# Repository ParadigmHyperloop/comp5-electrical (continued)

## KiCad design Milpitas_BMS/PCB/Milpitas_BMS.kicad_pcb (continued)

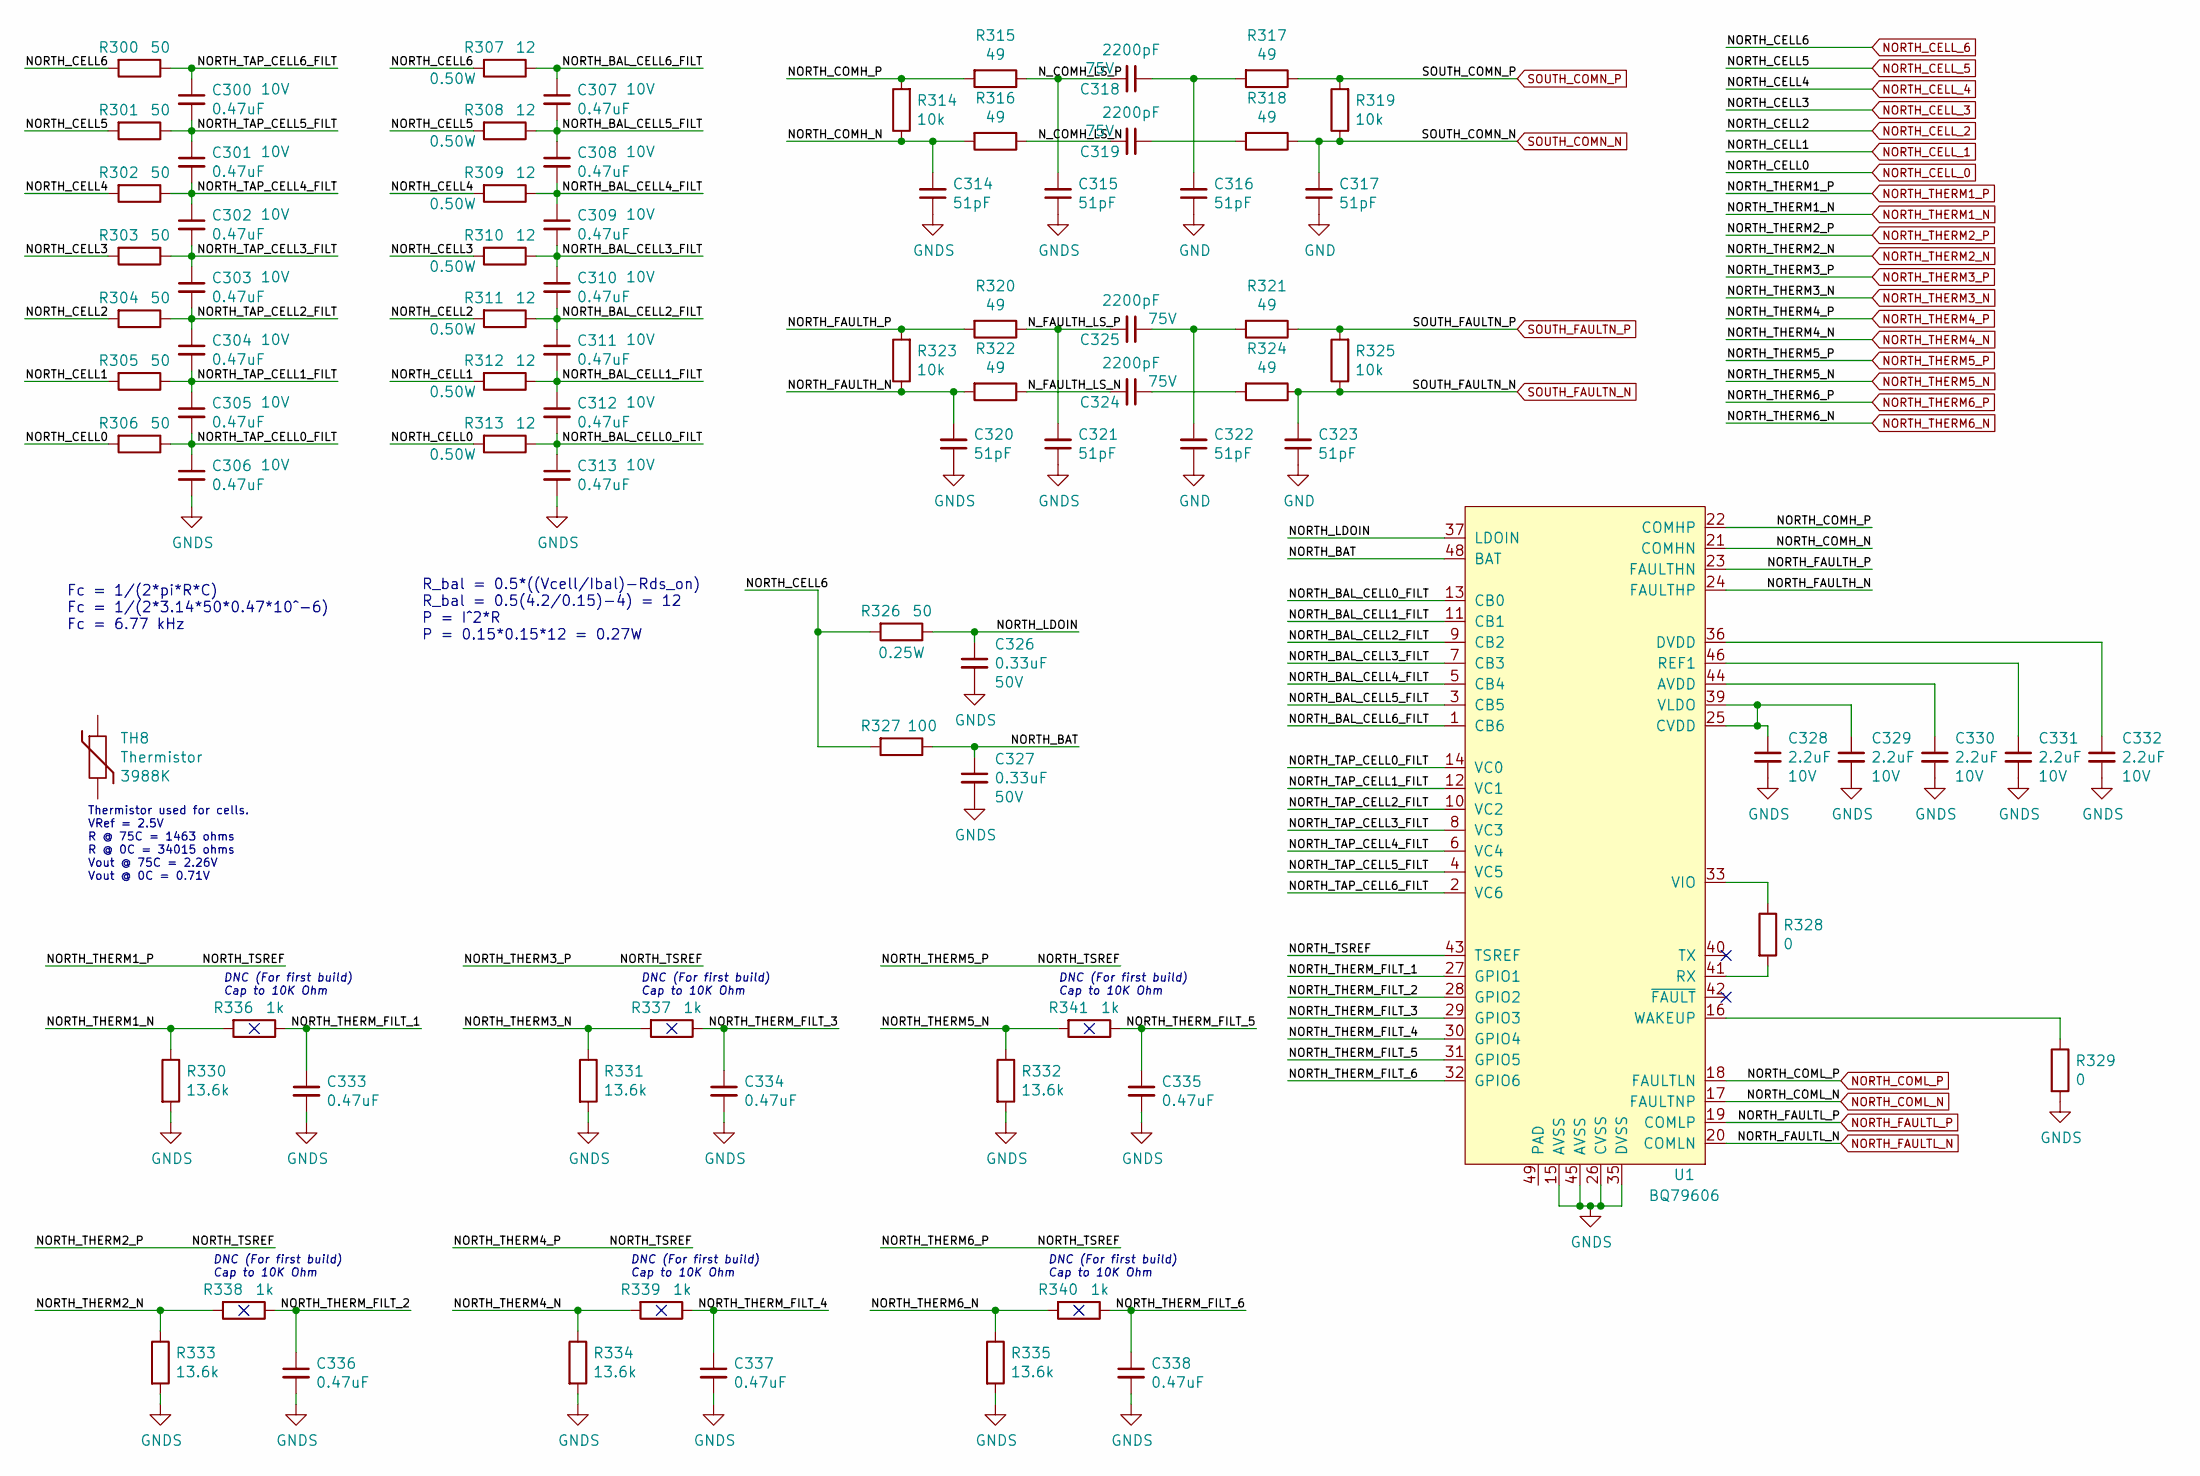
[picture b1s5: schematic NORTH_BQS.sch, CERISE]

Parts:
C300, C301, C302, C303, C304, C305, C306, C307, C308, C309, C310, C311, C312, C313: 0.47uF; C_0603_1608Metric; Voltage 10V
C314, C315, C316, C317, C320, C321, C322, C323: 51pF; C_0603_1608Metric
C318, C319, C324, C325: 2200pF; C_0603_1608Metric; Voltage 75V
C326, C327: 0.33uF; C_0603_1608Metric; Voltage 50V
C328, C329, C330, C331, C332: 2.2uF; C_0603_1608Metric; Voltage 10V
C333, C334, C335, C336, C337, C338: 0.47uF; C_0603_1608Metric
R300, R301, R302, R303, R304, R305, R306, R326: 50; R_0603_1608Metric
R307, R308, R309, R310, R311, R312, R313: 12; R_0603_1608Metric
R314, R319, R323, R325: 10k; R_0603_1608Metric
R315, R316, R317, R318, R320, R321, R322, R324: 49; R_0603_1608Metric
R327: 100; R_0603_1608Metric
R328, R329: 0; R_0603_1608Metric
R330, R331, R332, R333, R334, R335: 13.6k; R_0603_1608Metric
R336, R337, R338, R339, R340, R341: 1k; R_0603_1608Metric
TH8: Thermistor
U1: BQ79606; LQFP-48-1EP_7x7mm_P0.5mm_EP3.6x3.6mm_ThermalVias; Digikey 296-BQ79606APHPTQ1CT-ND

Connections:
/NORTH_BQ/NORTH_BAL_CELL0_FILT: C312.2, C313.1, R313.1, U1.13 (CB0)
/NORTH_BQ/NORTH_BAL_CELL1_FILT: C311.2, C312.1, R312.1, U1.11 (CB1)
/NORTH_BQ/NORTH_BAL_CELL2_FILT: C310.2, C311.1, R311.1, U1.9 (CB2)
/NORTH_BQ/NORTH_BAL_CELL3_FILT: C309.2, C310.1, R310.1, U1.7 (CB3)
/NORTH_BQ/NORTH_BAL_CELL4_FILT: C308.2, C309.1, R309.1, U1.5 (CB4)
/NORTH_BQ/NORTH_BAL_CELL5_FILT: C307.2, C308.1, R308.1, U1.3 (CB5)
/NORTH_BQ/NORTH_BAL_CELL6_FILT: C307.1, R307.1, U1.1 (CB6)
/NORTH_BQ/NORTH_BAT: C327.1, R327.1, U1.48 (BAT)
/NORTH_BQ/NORTH_COMH_N: C314.2, R314.1, R316.2, U1.21 (COMHN)
/NORTH_BQ/NORTH_COMH_P: R314.2, R315.2, U1.22 (COMHP)
/NORTH_BQ/NORTH_FAULTH_N: C320.2, R322.2, R323.1, U1.24 (FAULTHP)
/NORTH_BQ/NORTH_FAULTH_P: R320.2, R323.2, U1.23 (FAULTHN)
/NORTH_BQ/NORTH_LDOIN: C326.1, R326.1, U1.37 (LDOIN)
/NORTH_BQ/NORTH_TAP_CELL0_FILT: C305.2, C306.1, R306.1, U1.14 (VC0)
/NORTH_BQ/NORTH_TAP_CELL1_FILT: C304.2, C305.1, R305.1, U1.12 (VC1)
/NORTH_BQ/NORTH_TAP_CELL2_FILT: C303.2, C304.1, R304.1, U1.10 (VC2)
/NORTH_BQ/NORTH_TAP_CELL3_FILT: C302.2, C303.1, R303.1, U1.8 (VC3)
/NORTH_BQ/NORTH_TAP_CELL4_FILT: C301.2, C302.1, R302.1, U1.6 (VC4)
/NORTH_BQ/NORTH_TAP_CELL5_FILT: C300.2, C301.1, R301.1, U1.4 (VC5)
/NORTH_BQ/NORTH_TAP_CELL6_FILT: C300.1, R300.1, U1.2 (VC6)
/NORTH_BQ/NORTH_THERM_FILT_1: C333.1, R336.1, U1.27 (GPIO1)
/NORTH_BQ/NORTH_THERM_FILT_2: C336.1, R338.1, U1.28 (GPIO2)
/NORTH_BQ/NORTH_THERM_FILT_3: C334.1, R337.1, U1.29 (GPIO3)
/NORTH_BQ/NORTH_THERM_FILT_4: C337.1, R339.1, U1.30 (GPIO4)
/NORTH_BQ/NORTH_THERM_FILT_5: C335.1, R341.1, U1.31 (GPIO5)
/NORTH_BQ/NORTH_THERM_FILT_6: C338.1, R340.1, U1.32 (GPIO6)
/NORTH_BQ/N_COMH_LS_N: C319.2, R316.1
/NORTH_BQ/N_COMH_LS_P: C315.2, C318.2, R315.1
/NORTH_BQ/N_FAULTH_LS_N: C324.2, R322.1
/NORTH_BQ/N_FAULTH_LS_P: C321.2, C325.2, R320.1
GNDS: C306.2, C313.2, C314.1, C315.1, C320.1, C321.1, C326.2, C327.2, C328.2, C329.2, C330.2, C331.2, C332.2, C333.2, C334.2, C335.2, C336.2, C337.2, C338.2, R329.2, R330.2, R331.2, R332.2, R333.2, R334.2, R335.2, U1.15 (AVSS), U1.26 (CVSS), U1.35 (DVSS), U1.45 (AVSS), U1.49 (PAD); also elsewhere on the board
NORTH_CELL_0: R306.2, R313.2; also elsewhere on the board
NORTH_CELL_1: R305.2, R312.2; also elsewhere on the board
NORTH_CELL_2: R304.2, R311.2; also elsewhere on the board
NORTH_CELL_3: R303.2, R310.2; also elsewhere on the board
NORTH_CELL_4: R302.2, R309.2; also elsewhere on the board
NORTH_CELL_5: R301.2, R308.2; also elsewhere on the board
NORTH_CELL_6: R300.2, R307.2, R326.2, R327.2; also elsewhere on the board
NORTH_COML_N: U1.17 (FAULTNP); also elsewhere on the board
NORTH_COML_P: U1.18 (FAULTLN); also elsewhere on the board
NORTH_FAULTL_N: U1.20 (COMLN); also elsewhere on the board
NORTH_FAULTL_P: U1.19 (COMLP); also elsewhere on the board
NORTH_THERM1_N: R330.1, R336.2; also elsewhere on the board
NORTH_THERM1_P: U1.43 (TSREF); also elsewhere on the board
NORTH_THERM2_N: R333.1, R338.2; also elsewhere on the board
NORTH_THERM3_N: R331.1, R337.2; also elsewhere on the board
NORTH_THERM4_N: R334.1, R339.2; also elsewhere on the board
NORTH_THERM5_N: R332.1, R341.2; also elsewhere on the board
NORTH_THERM6_N: R335.1, R340.2; also elsewhere on the board
unnamed: C316.2, C318.1, R317.2
unnamed: C319.1, R318.2
unnamed: C322.2, C325.1, R321.2
unnamed: C324.1, R324.2
unnamed: C328.1, C329.1, U1.25 (CVDD), U1.39 (VLDO)
unnamed: C330.1, U1.44 (AVDD)
unnamed: C331.1, U1.46 (REF1)
unnamed: C332.1, U1.36 (DVDD)
unnamed: R328.1, U1.33 (VIO)
unnamed: R328.2, U1.41 (RX)
unnamed: R329.1, U1.16 (WAKEUP)
SOUTH_COMN_N: C317.2, R318.1, R319.1; also elsewhere on the board
SOUTH_COMN_P: R317.1, R319.2; also elsewhere on the board
SOUTH_FAULTN_N: C323.2, R324.1, R325.1; also elsewhere on the board
SOUTH_FAULTN_P: R321.1, R325.2; also elsewhere on the board

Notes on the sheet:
R_bal = 0.5*((Vcell/Ibal)-Rds_on) R_bal = 0.5(4.2/0.15)-4) = 12 P = I^2*R P = 0.15*0.15*12 = 0.27W
DNC (For first build) Cap to 10K Ohm
Fc = 1/(2*pi*R*C) Fc = 1/(2*3.14*50*0.47*10^-6) Fc = 6.77 kHz
Thermistor used for cells. VRef = 2.5V R @ 75C = 1463 ohms R @ 0C = 34015 ohms Vout @ 75C = 2.26V Vout @ 0C = 0.71V

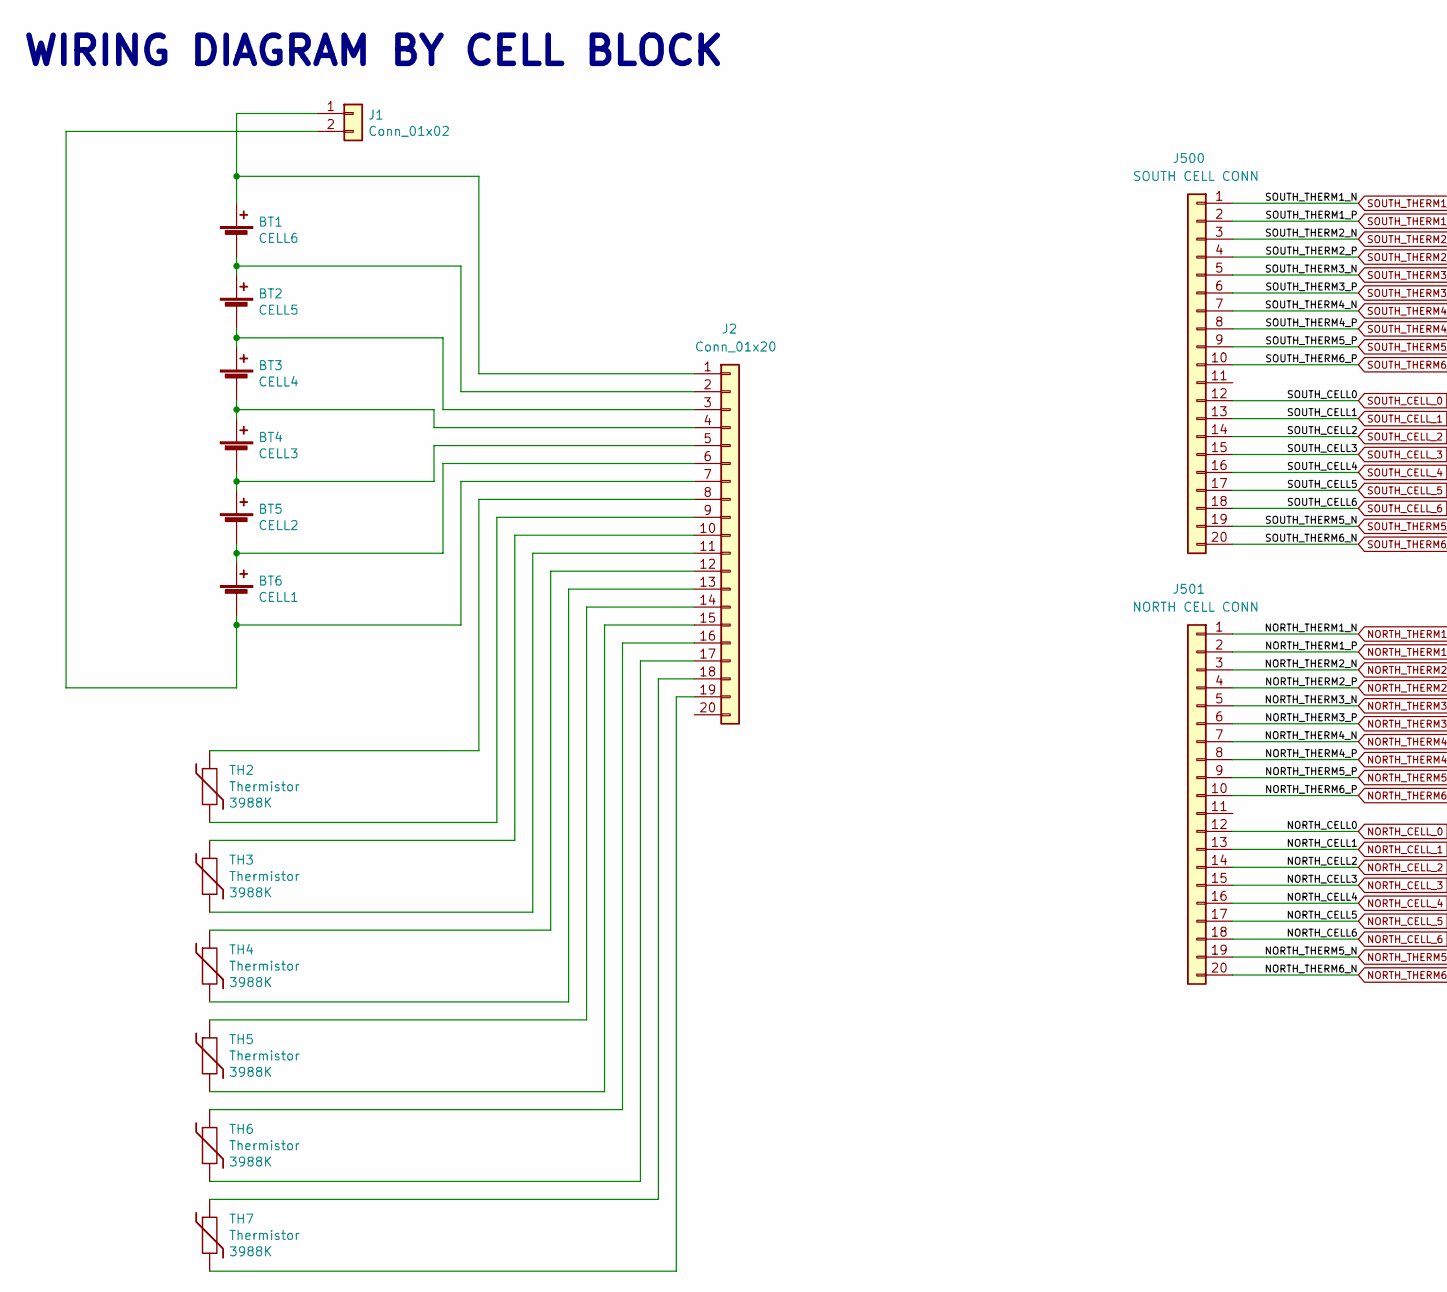
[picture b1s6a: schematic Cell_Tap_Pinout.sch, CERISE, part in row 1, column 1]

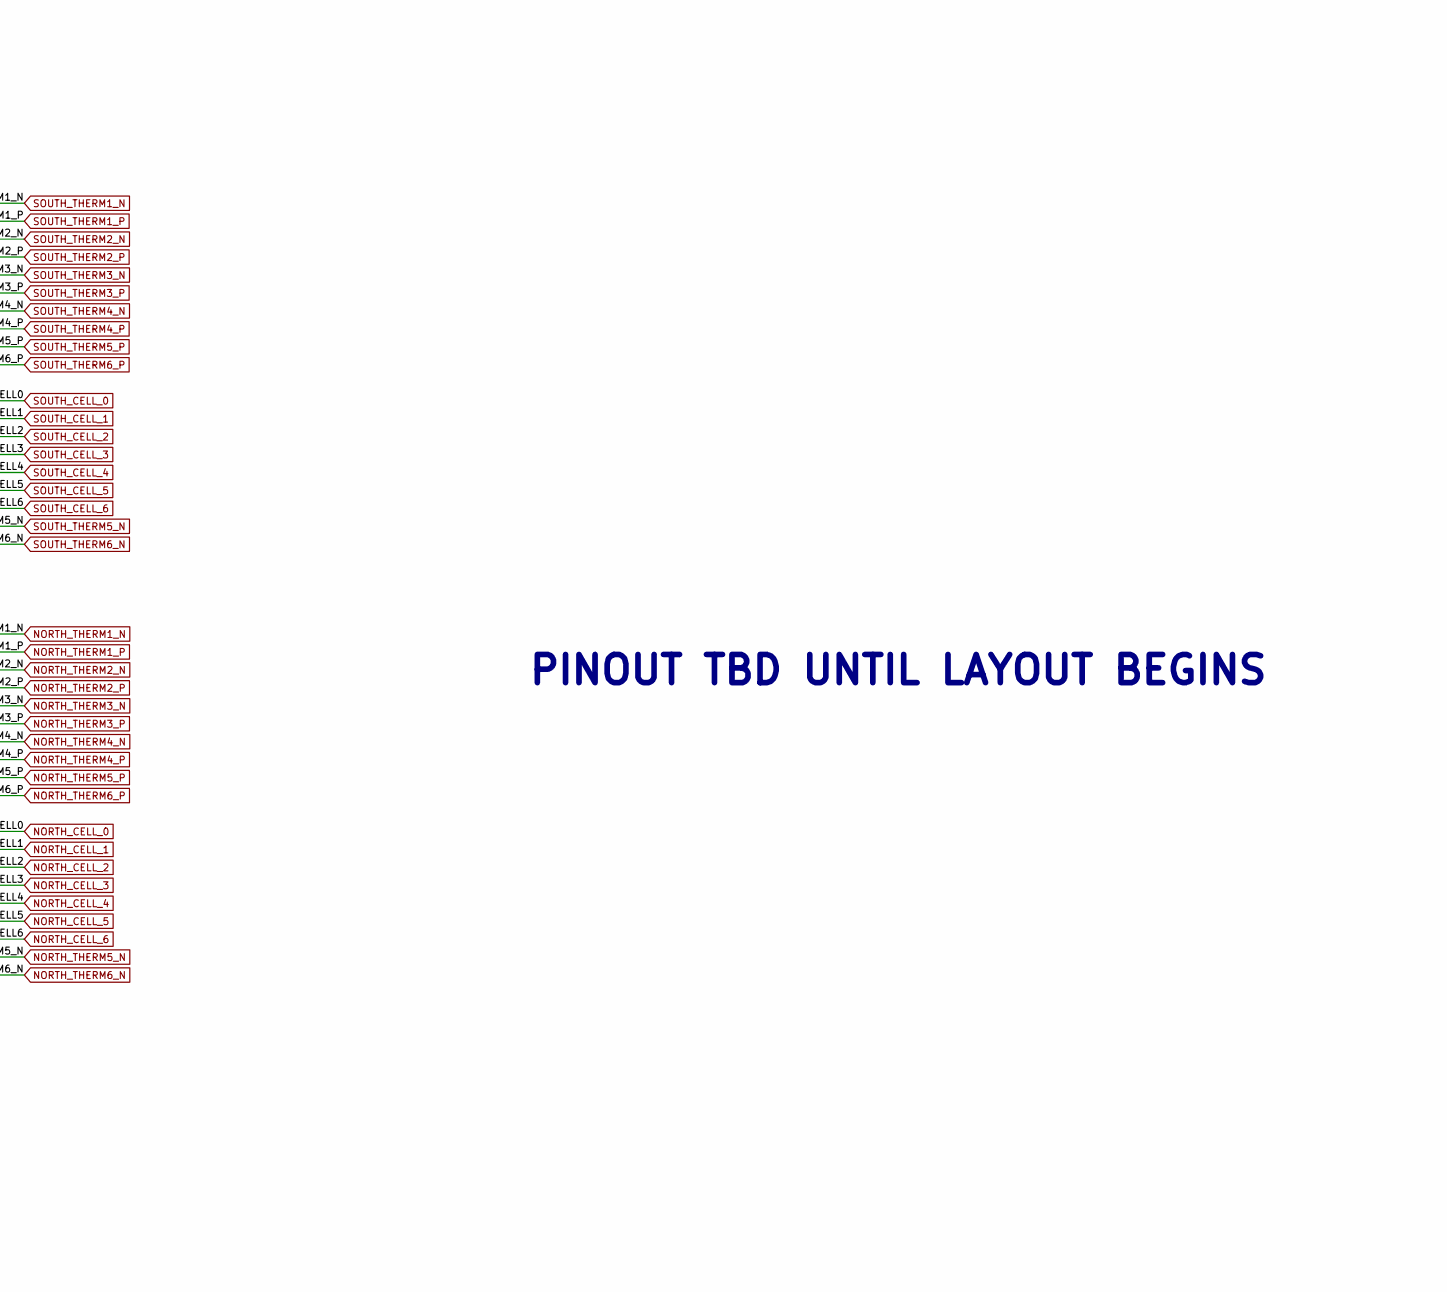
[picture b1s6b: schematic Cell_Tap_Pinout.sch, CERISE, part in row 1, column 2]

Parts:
BT1: CELL6
BT2: CELL5
BT3: CELL4
BT4: CELL3
BT5: CELL2
BT6: CELL1
J1: Conn_01x02
J2: Conn_01x20
J500: SOUTH CELL CONN; Molex_Micro-Fit_3.0_43045-2000_2x10_P3.00mm_Horizontal; Digikey WM4726-ND
J501: NORTH CELL CONN; Molex_Micro-Fit_3.0_43045-2000_2x10_P3.00mm_Horizontal; Digikey WM4726-ND
TH2, TH3, TH4, TH5, TH6, TH7: Thermistor

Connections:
NORTH_CELL_0: J501.12; also elsewhere on the board
NORTH_CELL_1: J501.13; also elsewhere on the board
NORTH_CELL_2: J501.14; also elsewhere on the board
NORTH_CELL_3: J501.15; also elsewhere on the board
NORTH_CELL_4: J501.16; also elsewhere on the board
NORTH_CELL_5: J501.17; also elsewhere on the board
NORTH_CELL_6: J501.18; also elsewhere on the board
NORTH_THERM1_N: J501.1; also elsewhere on the board
NORTH_THERM1_P: J501.2, J501.4, J501.6, J501.8, J501.9, J501.10; also elsewhere on the board
NORTH_THERM2_N: J501.3; also elsewhere on the board
NORTH_THERM3_N: J501.5; also elsewhere on the board
NORTH_THERM4_N: J501.7; also elsewhere on the board
NORTH_THERM5_N: J501.19; also elsewhere on the board
NORTH_THERM6_N: J501.20; also elsewhere on the board
unnamed: BT1.1 (+), J1.1, J2.1
unnamed: BT1.2 (-), BT2.1 (+), J2.2
unnamed: BT2.2 (-), BT3.1 (+), J2.3
unnamed: BT3.2 (-), BT4.1 (+), J2.4
unnamed: BT4.2 (-), BT5.1 (+), J2.5
unnamed: BT5.2 (-), BT6.1 (+), J2.6
unnamed: BT6.2 (-), J1.2, J2.7
unnamed: J2.8, TH2.1
unnamed: J2.9, TH2.2
unnamed: J2.10, TH3.1
unnamed: J2.11, TH3.2
unnamed: J2.12, TH4.1
unnamed: J2.13, TH4.2
unnamed: J2.14, TH5.1
unnamed: J2.15, TH5.2
unnamed: J2.16, TH6.1
unnamed: J2.17, TH6.2
unnamed: J2.18, TH7.1
unnamed: J2.19, TH7.2
SOUTH_CELL_0: J500.12; also elsewhere on the board
SOUTH_CELL_1: J500.13; also elsewhere on the board
SOUTH_CELL_2: J500.14; also elsewhere on the board
SOUTH_CELL_3: J500.15; also elsewhere on the board
SOUTH_CELL_4: J500.16; also elsewhere on the board
SOUTH_CELL_5: J500.17; also elsewhere on the board
SOUTH_CELL_6: J500.18; also elsewhere on the board
SOUTH_THERM1_N: J500.1; also elsewhere on the board
SOUTH_THERM1_P: J500.2, J500.4, J500.6, J500.8, J500.9, J500.10; also elsewhere on the board
SOUTH_THERM2_N: J500.3; also elsewhere on the board
SOUTH_THERM3_N: J500.5; also elsewhere on the board
SOUTH_THERM4_N: J500.7; also elsewhere on the board
SOUTH_THERM5_N: J500.19; also elsewhere on the board
SOUTH_THERM6_N: J500.20; also elsewhere on the board

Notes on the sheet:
WIRING DIAGRAM BY CELL BLOCK
PINOUT TBD UNTIL LAYOUT BEGINS

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
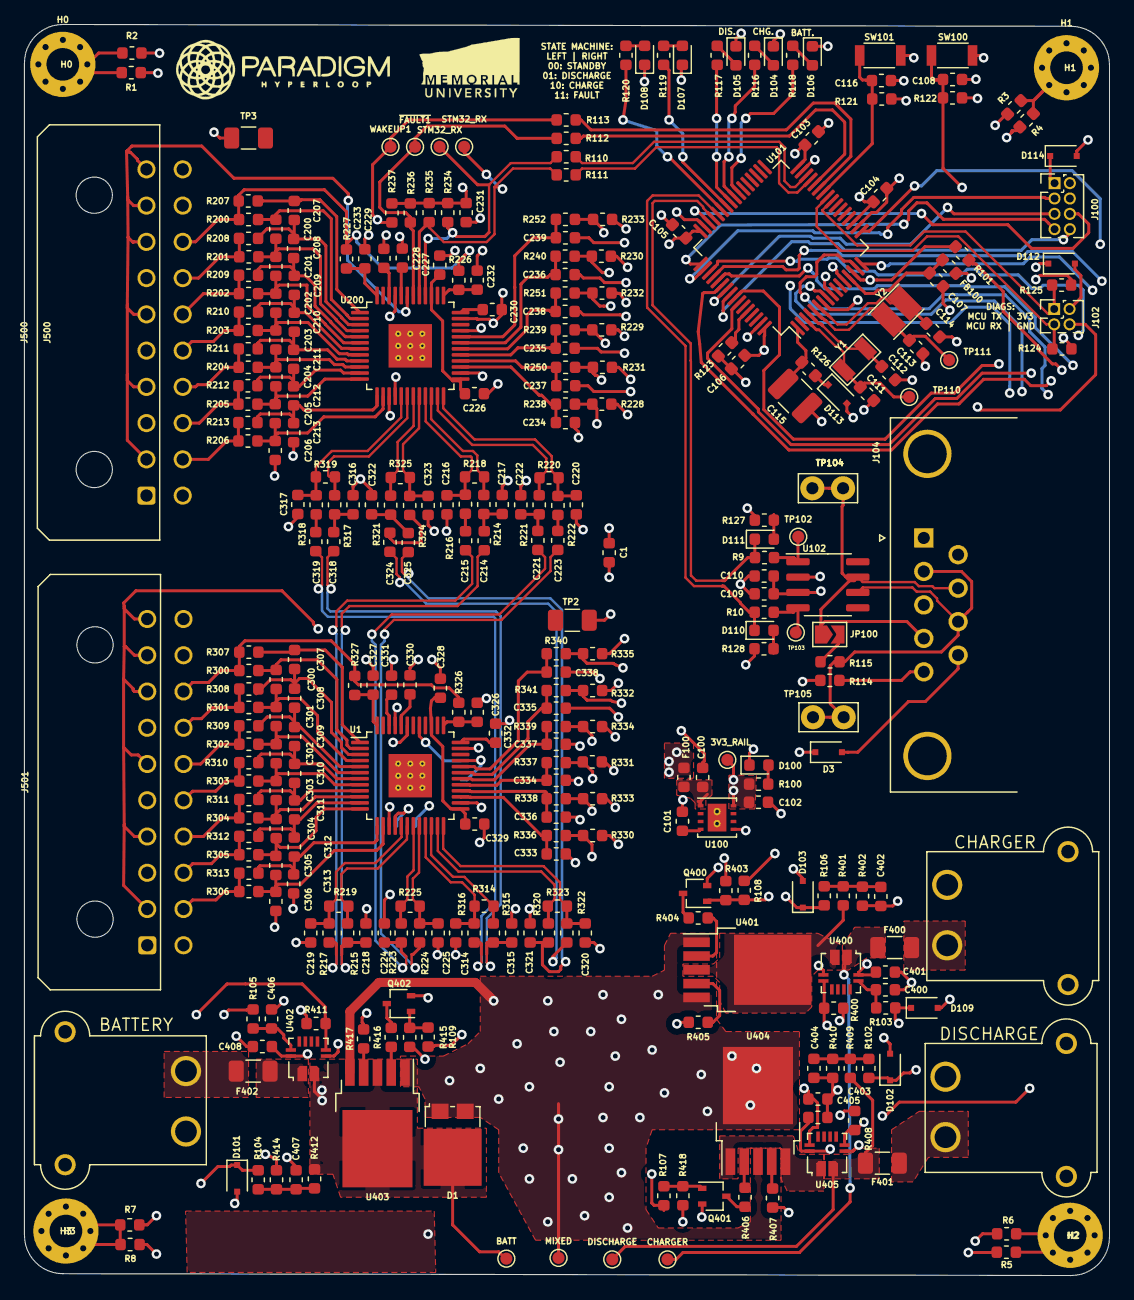
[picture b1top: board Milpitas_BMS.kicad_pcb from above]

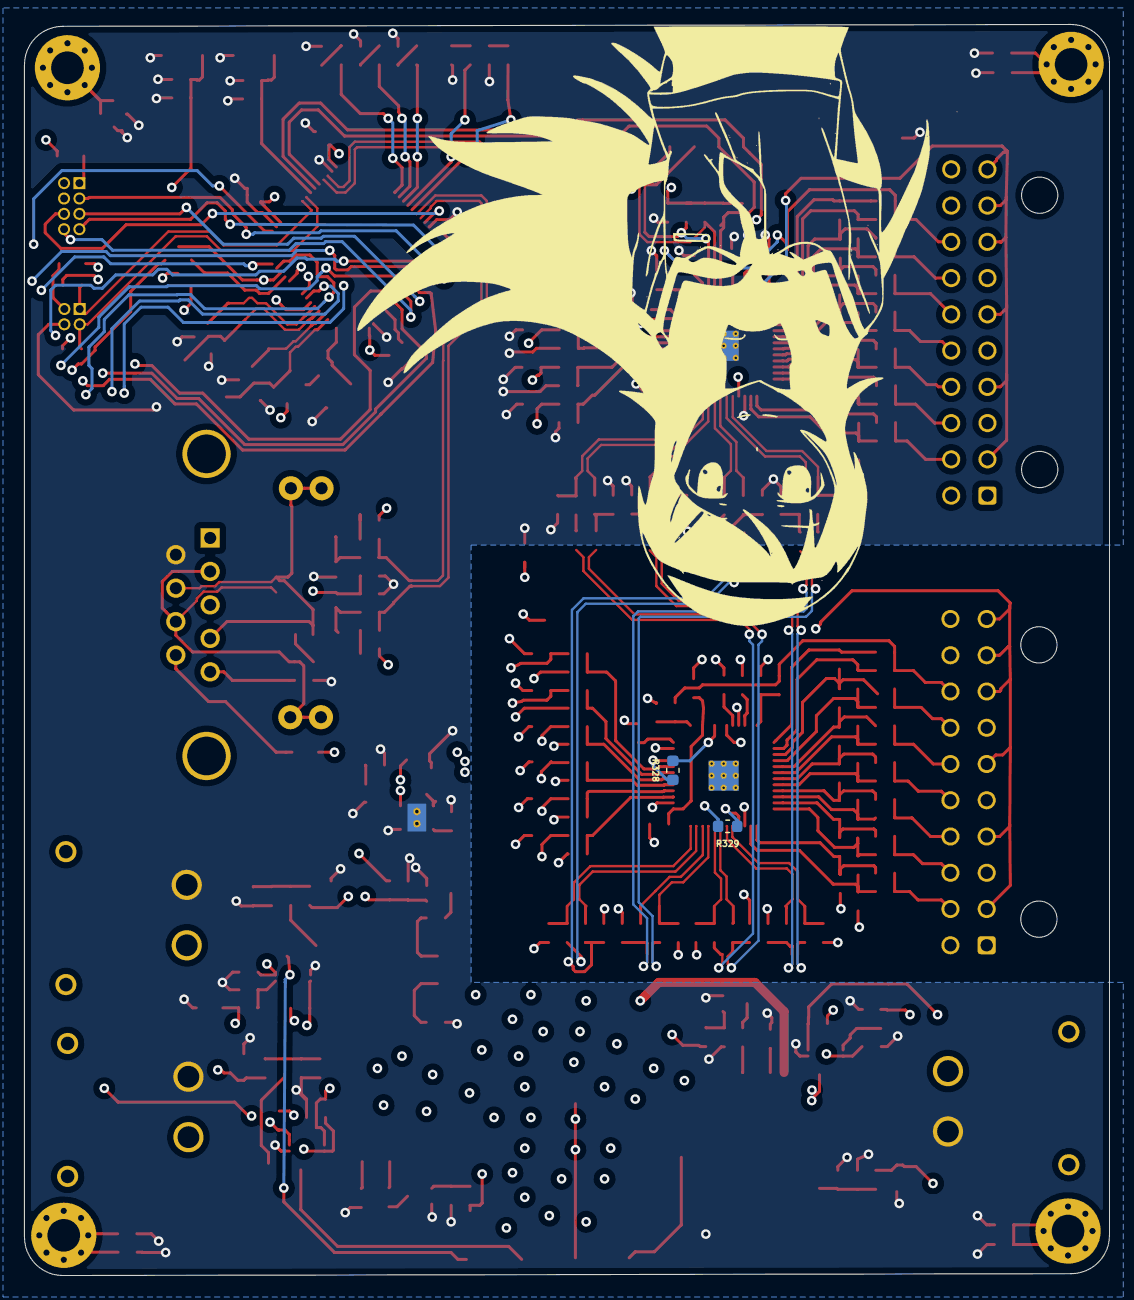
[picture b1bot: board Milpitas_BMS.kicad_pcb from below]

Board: 4 copper layers, 89.8 x 103.5 mm, 318 parts (2 on the bottom side), 214 nets.

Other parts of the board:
3V3_RAIL: 3V3_RAIL; TestPoint_Pad_D1.0mm
BATT: BATT_RAIL; TestPoint_Pad_D1.0mm
BATTERY: BATT_PWR_INPUT; XT30-RIGHT-ANGLE
CHARGER: CHARGER; TestPoint_Pad_D1.0mm
CHARGER#2: CHG INPUT; XT30-RIGHT-ANGLE
DISCHARGE: DISCHARGE; TestPoint_Pad_D1.0mm
DISCHARGE#2: POWER_OUTPUT; XT30-RIGHT-ANGLE
MIXED: POWER_MIX; TestPoint_Pad_D1.0mm
STM32_RX: BMS_UART_TX; TestPoint_Pad_D1.0mm
STM32_RX#2: BMS_UART_RX; TestPoint_Pad_D1.0mm

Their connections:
+BATT: BATT.1; also elsewhere on the board
/INPUT_OUTPUT/CHG_RAW: CHARGER.1; also elsewhere on the board
/INPUT_OUTPUT/DIS_MSRD: DISCHARGE.1; also elsewhere on the board
/INPUT_OUTPUT/MIXED_PWR_PLANE: MIXED.1; also elsewhere on the board
unnamed 171: CHARGER#2.2; also elsewhere on the board
unnamed 172: DISCHARGE#2.2; also elsewhere on the board
unnamed 173: BATTERY.2; also elsewhere on the board
STM32_UART_N: STM32_RX#2.1; also elsewhere on the board
STM32_UART_P: STM32_RX.1; also elsewhere on the board

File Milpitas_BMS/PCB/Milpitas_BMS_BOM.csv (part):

"Source:","C:\comp5-electrical\Milpitas_BMS\PCB\Milpitas_BMS.sch"
"Date:","4/12/2020 2:36:05 PM"
"Tool:","Eeschema (5.1.5)-3"
"Generator:","C:\Program Files\KiCad\bin\scripting\plugins/bom_csv_grouped_by_value.py"
"Component Count:","328"

"Individual Components:"

"Item","Qty","Reference(s)","Value","LibPart","Footprint","Datasheet","Beta","Digikey","Power","Voltage"
"","","3V3_RAIL1","3V3_RAIL","Connector:TestPoint","TestPoint:TestPoint_Pad_D1.0mm","","","","",""
"","","BATT1","BATT_RAIL","Connector:TestPoint","TestPoint:TestPoint_Pad_D1.0mm","","","","",""
"","","BT1","CELL6","Device:Battery_Cell","","~","","","",""
"","","BT2","CELL5","Device:Battery_Cell","","~","","","",""
"","","BT3","CELL4","Device:Battery_Cell","","~","","","",""
"","","BT4","CELL3","Device:Battery_Cell","","~","","","",""
"","","BT5","CELL2","Device:Battery_Cell","","~","","","",""
"","","BT6","CELL1","Device:Battery_Cell","","~","","","",""
"","","C1","CXX","Device:C_Small","Capacitor_SMD:C_0603_1608Metric","~","","399-7880-1-ND","","75V"
"","","C100","1uF","Device:C_Small","Capacitor_SMD:C_0603_1608Metric","~","","1276-1860-1-ND","","50V"
"","","C101","0.1uF","Device:C_Small","Capacitor_SMD:C_0603_1608Metric","~","","399-7845-1-ND","","50V"
"","","C102","1uF","Device:C_Small","Capacitor_SMD:C_0603_1608Metric","~","","1276-1860-1-ND","","6V"
"","","C103","0.47uF","Device:C_Small","Capacitor_SMD:C_0603_1608Metric","~","","1292-1451-1-ND","",""
"","","C104","0.47uF","Device:C_Small","Capacitor_SMD:C_0603_1608Metric","~","","1292-1451-1-ND","",""
"","","C105","0.47uF","Device:C_Small","Capacitor_SMD:C_0603_1608Metric","~","","1292-1451-1-ND","",""
"","","C106","0.47uF","Device:C_Small","Capacitor_SMD:C_0603_1608Metric","~","","1292-1451-1-ND","",""
"","","C107","0.47uF","Device:C_Small","Capacitor_SMD:C_0603_1608Metric","~","","1292-1451-1-ND","",""
"","","C108","0.47uF","Device:C_Small","Capacitor_SMD:C_0603_1608Metric","~","","1292-1451-1-ND","",""
"","","C109","0.47uF","Device:C_Small","Capacitor_SMD:C_0603_1608Metric","~","","1292-1451-1-ND","",""
"","","C110","2200pF","Device:C_Small","Capacitor_SMD:C_0603_1608Metric","~","","399-7880-1-ND","",""
"","","C111","7pF","Device:C_Small","Capacitor_SMD:C_0603_1608Metric","~","","490-11478-1-ND","",""
"","","C112","7pF","Device:C_Small","Capacitor_SMD:C_0603_1608Metric","~","","490-11478-1-ND","",""
"","","C113","8pF","Device:C_Small","Capacitor_SMD:C_0603_1608Metric","~","","490-9670-1-ND","",""
"","","C114","8pF","Device:C_Small","Capacitor_SMD:C_0603_1608Metric","~","","490-9670-1-ND","",""
"","","C115","11mF","Device:C_Small","Capacitor_SMD:C_1210_3225Metric","https://media.digikey.com/pdf/Data%20Sheets/Seiko%20Instrume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","","728-1127-1-ND","",""
"","","C116","0.47uF","Device:C_Small","Capacitor_SMD:C_0603_1608Metric","~","","1292-1451-1-ND","",""
"","","C200","0.47uF","Device:C_Small","Capacitor_SMD:C_0603_1608Metric","~","","1292-1451-1-ND","","10V"
"","","C201","0.47uF","Device:C_Small","Capacitor_SMD:C_0603_1608Metric","~","","1292-1451-1-ND","","10V"
"","","C202","0.47uF","Device:C_Small","Capacitor_SMD:C_0603_1608Metric","~","","1292-1451-1-ND","","10V"
"","","C203","0.47uF","Device:C_Small","Capacitor_SMD:C_0603_1608Metric","~","","1292-1451-1-ND","","10V"
"","","C204","0.47uF","Device:C_Small","Capacitor_SMD:C_0603_1608Metric","~","","1292-1451-1-ND","","10V"
"","","C205","0.47uF","Device:C_Small","Capacitor_SMD:C_0603_1608Metric","~","","1292-1451-1-ND","","10V"
"","","C206","0.47uF","Device:C_Small","Capacitor_SMD:C_0603_1608Metric","~","","1292-1451-1-ND","","10V"
"","","C207","0.47uF","Device:C_Small","Capacitor_SMD:C_0603_1608Metric","~","","1292-1451-1-ND","","10V"
"","","C208","0.47uF","Device:C_Small","Capacitor_SMD:C_0603_1608Metric","~","","1292-1451-1-ND","","10V"
"","","C209","0.47uF","Device:C_Small","Capacitor_SMD:C_0603_1608Metric","~","","1292-1451-1-ND","","10V"
"","","C210","0.47uF","Device:C_Small","Capacitor_SMD:C_0603_1608Metric","~","","1292-1451-1-ND","","10V"
"","","C211","0.47uF","Device:C_Small","Capacitor_SMD:C_0603_1608Metric","~","","1292-1451-1-ND","","10V"
"","","C212","0.47uF","Device:C_Small","Capacitor_SMD:C_0603_1608Metric","~","","1292-1451-1-ND","","10V"
"","","C213","0.47uF","Device:C_Small","Capacitor_SMD:C_0603_1608Metric","~","","1292-1451-1-ND","","10V"
"","","C214","2200pF","Device:C_Small","Capacitor_SMD:C_0603_1608Metric","~","","399-7880-1-ND","","75V"
"","","C215","2200pF","Device:C_Small","Capacitor_SMD:C_0603_1608Metric","~","","399-7880-1-ND","","75V"
"","","C216","51pF","Device:C_Small","Capacitor_SMD:C_0603_1608Metric","~","","1276-2310-1-ND","",""
"","","C217","51pF","Device:C_Small","Capacitor_SMD:C_0603_1608Metric","~","","1276-2310-1-ND","",""
"","","C218","51pF","Device:C_Small","Capacitor_SMD:C_0603_1608Metric","~","","1276-2310-1-ND","",""
"","","C219","51pF","Device:C_Small","Capacitor_SMD:C_0603_1608Metric","~","","1276-2310-1-ND","",""
"","","C220","51pF","Device:C_Small","Capacitor_SMD:C_0603_1608Metric","~","","1276-2310-1-ND","",""
"","","C221","2200pF","Device:C_Small","Capacitor_SMD:C_0603_1608Metric","~","","399-7880-1-ND","","75V"
"","","C222","51pF","Device:C_Small","Capacitor_SMD:C_0603_1608Metric","~","","1276-2310-1-ND","",""
"","","C223","2200pF","Device:C_Small","Capacitor_SMD:C_0603_1608Metric","~","","399-7880-1-ND","","75V"
"","","C224","51pF","Device:C_Small","Capacitor_SMD:C_0603_1608Metric","~","","1276-2310-1-ND","",""
"","","C225","51pF","Device:C_Small","Capacitor_SMD:C_0603_1608Metric","~","","1276-2310-1-ND","",""
"","","C226","2.2uF","Device:C_Small","Capacitor_SMD:C_0603_1608Metric","~","","1276-1085-1-ND","","10V"
"","","C227","2.2uF","Device:C_Small","Capacitor_SMD:C_0603_1608Metric","~","","1276-1085-1-ND","","10V"
"","","C228","2.2uF","Device:C_Small","Capacitor_SMD:C_0603_1608Metric","~","","1276-1085-1-ND","","10V"
"","","C229","2.2uF","Device:C_Small","Capacitor_SMD:C_0603_1608Metric","~","","1276-1085-1-ND","","10V"
"","","C230","2.2uF","Device:C_Small","Capacitor_SMD:C_0603_1608Metric","~","","1276-1085-1-ND","","10V"
"","","C231","2.2uF","Device:C_Small","Capacitor_SMD:C_0603_1608Metric","~","","1276-1085-1-ND","","10V"
"","","C232","0.33uF","Device:C_Small","Capacitor_SMD:C_0603_1608Metric","~","","445-7462-1-ND","","50V"
"","","C233","0.33uF","Device:C_Small","Capacitor_SMD:C_0603_1608Metric","~","","445-7462-1-ND","","50V"
"","","C234","0.47uF","Device:C_Small","Capacitor_SMD:C_0603_1608Metric","~","","1292-1451-1-ND","",""
"","","C235","0.47uF","Device:C_Small","Capacitor_SMD:C_0603_1608Metric","~","","1292-1451-1-ND","",""
"","","C236","0.47uF","Device:C_Small","Capacitor_SMD:C_0603_1608Metric","~","","1292-1451-1-ND","",""
"","","C237","0.47uF","Device:C_Small","Capacitor_SMD:C_0603_1608Metric","~","","1292-1451-1-ND","",""
"","","C238","0.47uF","Device:C_Small","Capacitor_SMD:C_0603_1608Metric","~","","1292-1451-1-ND","",""
"","","C239","0.47uF","Device:C_Small","Capacitor_SMD:C_0603_1608Metric","~","","1292-1451-1-ND","",""
"","","C300","0.47uF","Device:C_Small","Capacitor_SMD:C_0603_1608Metric","~","","1292-1451-1-ND","","10V"
"","","C301","0.47uF","Device:C_Small","Capacitor_SMD:C_0603_1608Metric","~","","1292-1451-1-ND","","10V"
"","","C302","0.47uF","Device:C_Small","Capacitor_SMD:C_0603_1608Metric","~","","1292-1451-1-ND","","10V"
"","","C303","0.47uF","Device:C_Small","Capacitor_SMD:C_0603_1608Metric","~","","1292-1451-1-ND","","10V"
"","","C304","0.47uF","Device:C_Small","Capacitor_SMD:C_0603_1608Metric","~","","1292-1451-1-ND","","10V"
"","","C305","0.47uF","Device:C_Small","Capacitor_SMD:C_0603_1608Metric","~","","1292-1451-1-ND","","10V"
"","","C306","0.47uF","Device:C_Small","Capacitor_SMD:C_0603_1608Metric","~","","1292-1451-1-ND","","10V"
"","","C307","0.47uF","Device:C_Small","Capacitor_SMD:C_0603_1608Metric","~","","1292-1451-1-ND","","10V"
"","","C308","0.47uF","Device:C_Small","Capacitor_SMD:C_0603_1608Metric","~","","1292-1451-1-ND","","10V"
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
